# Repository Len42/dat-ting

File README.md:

# dat ting

_Multi-function Eurorack module inspired by [dis ting](https://www.expert-sleepers.co.uk/disting.html)_

**dat ting** is a digital multi-function 10 HP Eurorack module using a [Daisy Seed](https://electro-smith.com/products/daisy-seed). Part of my [homebrew Eurorack synthesizer](https://lenp.net/synth/).

[See here](https://lenp.net/synth/dat-ting/) for more info.

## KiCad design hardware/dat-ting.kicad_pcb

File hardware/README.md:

# dat ting

**dat ting** is a digital multi-function 10 HP Eurorack module using a [Daisy Seed](https://electro-smith.com/products/daisy-seed).

[See here](https://lenp.net/synth/dat-ting/hardware.html) for more info.

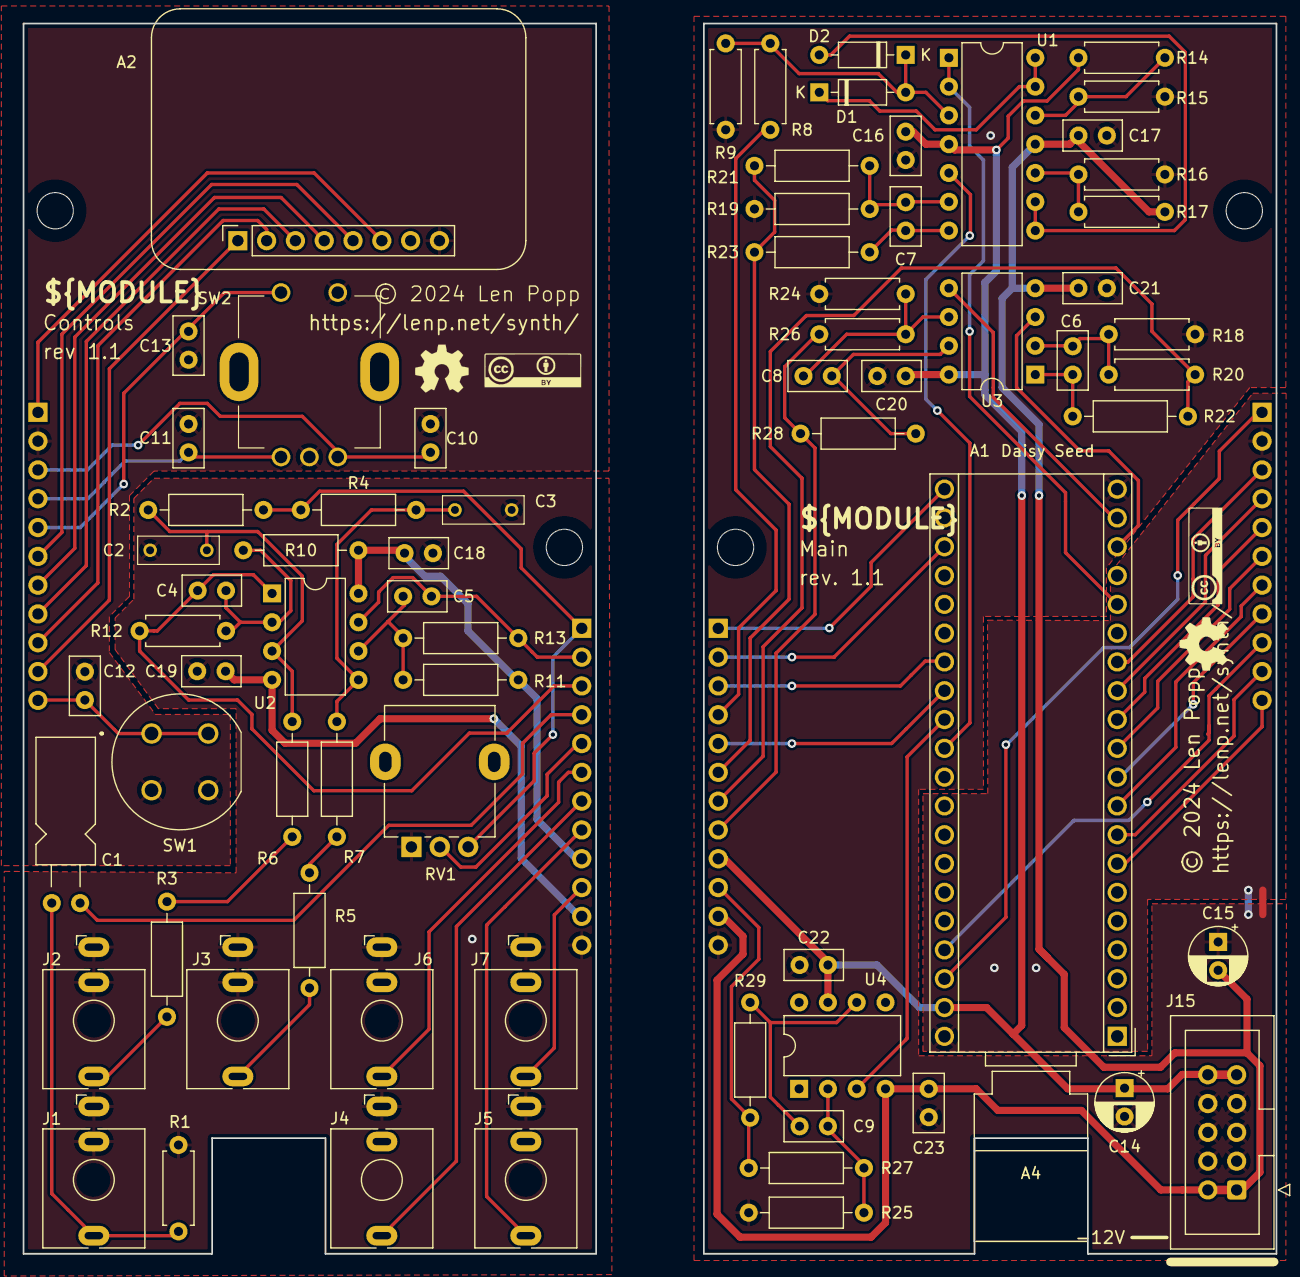
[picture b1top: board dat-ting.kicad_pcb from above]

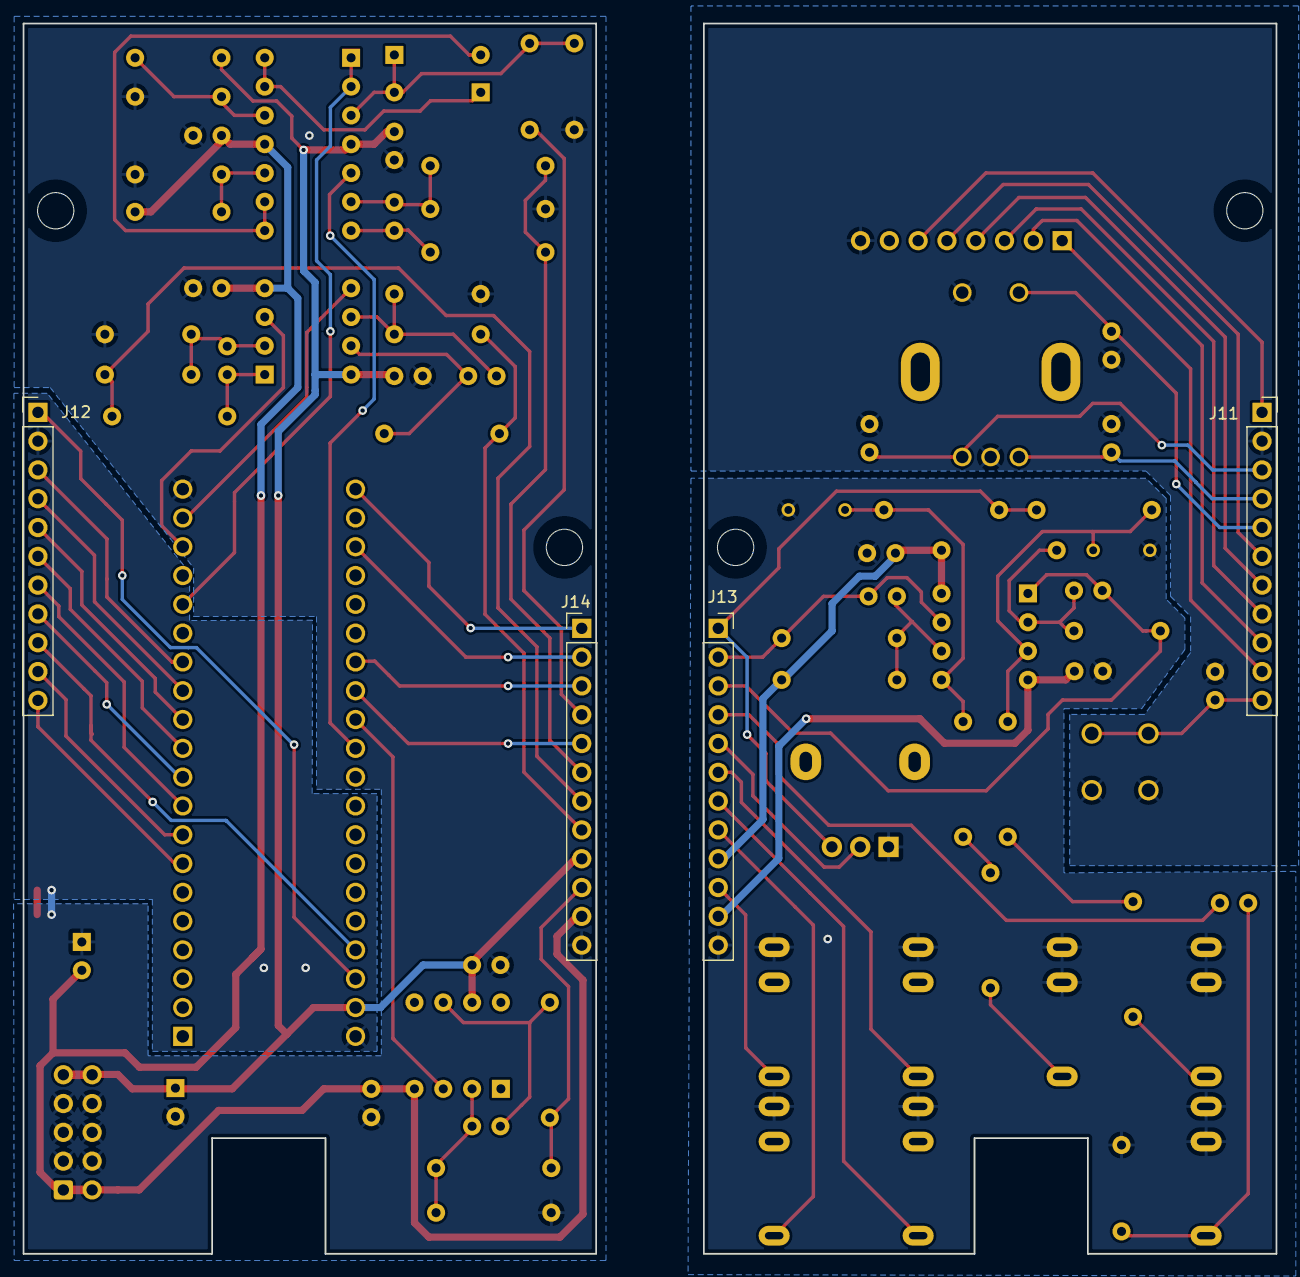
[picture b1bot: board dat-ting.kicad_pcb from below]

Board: 2 copper layers, 110.5 x 108.5 mm, 84 parts (4 on the bottom side), 49 nets.

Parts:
A1: Daisy_Seed; Module_Daisy_Seed
A2: OLED_SPI_128x32; OLED_SPI_128x32_0.91in_NoHoles
A4: Micro USB Adapter 90deg; USB-Micro-Adapter-90-Outline
C1: 4U7; C_Radial_L11.0mm_D5.0mm_P2.50mm_Horiz
C2, C3: 3N3; C_Rect_Kemet_L7.2mm_W2.5mm_P5mm
C4, C5: 5P6; C_Disc_D5.0mm_W2.5mm_P2.50mm
C6, C7, C8, C9: 47P; C_Disc_D5.0mm_W2.5mm_P2.50mm
C10, C11, C12, C13, C16, C17, C18, C19, C20, C21, C22, C23: 100N; C_Disc_D5.0mm_W2.5mm_P2.50mm
C14, C15: 10U; CP_Radial_D5.0mm_P2.50mm
D1, D2: 1N5711; D_DO-35_SOD27_P7.62mm_Horizontal
G1, G2: LOGO; Logo_CC_BY
G3, G4: LOGO; Logo_OSHW
H2, H4, H7, H9: MountingHole_M3; MountingHole_PCB_3.2mm_M3
J1, J2, J3, J4, J5, J6, J7: WQP-PJ398; Jack_3.5mm_QingPu_WQP-PJ398SM_Vertical
J11: Conn_Front_Left; PinSocket_1x11_P2.54mm_Vertical
J12: Conn_Back_Right; PinHeader_1x11_P2.54mm_Vertical
J13: Conn_Front_Right; PinSocket_1x12_P2.54mm_Vertical
J14: Conn_Back_Left; PinHeader_1x12_P2.54mm_Vertical
J15: Conn_Eurorack_10; IDC-Header-Eurorack-10-TH
R1: 1M; R_Axial_DIN0207_L6.3mm_D2.5mm_P7.62mm_Horizontal
R2, R4: 33K; R_Axial_DIN0207_L6.3mm_D2.5mm_P10.16mm_Horizontal
R3, R5, R6, R7: 120K; R_Axial_DIN0207_L6.3mm_D2.5mm_P10.16mm_Horizontal
R8, R20, R26: 100K; R_Axial_DIN0207_L6.3mm_D2.5mm_P7.62mm_Horizontal
R9: 33K; R_Axial_DIN0207_L6.3mm_D2.5mm_P7.62mm_Horizontal
R10, R11: 160K; R_Axial_DIN0207_L6.3mm_D2.5mm_P10.16mm_Horizontal
R12: 22K; R_Axial_DIN0207_L6.3mm_D2.5mm_P7.62mm_Horizontal
R13: 22K; R_Axial_DIN0207_L6.3mm_D2.5mm_P10.16mm_Horizontal
R14, R17: 130K; R_Axial_DIN0207_L6.3mm_D2.5mm_P7.62mm_Horizontal
R15, R16: 20K; R_Axial_DIN0207_L6.3mm_D2.5mm_P7.62mm_Horizontal
R18, R24: 36K; R_Axial_DIN0207_L6.3mm_D2.5mm_P7.62mm_Horizontal
R19, R25: 100K; R_Axial_DIN0207_L6.3mm_D2.5mm_P10.16mm_Horizontal
R21, R27: 200K; R_Axial_DIN0207_L6.3mm_D2.5mm_P10.16mm_Horizontal
R22, R23, R28, R29: 51R; R_Axial_DIN0207_L6.3mm_D2.5mm_P10.16mm_Horizontal
RV1: 100K; Potentiometer_Alpha_RD901F-40-00D_Single_Vertical
SW1: C&K_D6R; SW_Push_C&K_D6R
SW2: PEC11R; Encoder_Bourns_PEC11R_Switch
U1: TL074; DIP-14_W7.62mm
U2, U3: TL072; DIP-8_W7.62mm
U4: TL071; DIP-8_W7.62mm

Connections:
+3V3: A1.38 (3v3D), A2.6 (VIN), J11.1, J12.1
+3V3REF: A1.21 (3v3A), J13.1, J14.1, R2.1, R4.1, RV1.3
+12V: A1.39 (VIN), C14.1, C16.1, C18.1, C20.1, C22.1, J13.9, J14.9, J15.9 (+12V), J15.10, R10.2, R11.2, R14.1, U1.4 (V+), U2.8 (V+), U3.8 (V+), U4.7 (V+)
-12V: C15.2, C17.2, C19.2, C21.2, C23.2, J13.11, J14.11, J15.1 (-12V), J15.2, R17.1, U1.11 (V-), U2.4 (V-), U3.4 (V-), U4.4 (V-)
/+CLAMP: D1.1 (K), U1.13 (-), U1.14
/-CLAMP: D2.2 (A), U1.8, U1.9 (-)
ENC-A: A1.13 (D12), C11.1, J11.4, J12.4, SW2.A
ENC-B: A1.14 (D13), C10.1, J11.3, J12.3, SW2.B
ENC-SW: A1.12 (D11), C13.1, J11.5, J12.5, SW2.S1
GND: A1.20 (AGND), A1.40 (GND), A2.8 (GND), C2.2, C3.2, C10.2, C11.2, C12.2, C13.2, C14.2, C15.1, C16.2, C17.1, C18.2, C19.1, C20.2, C21.1, C22.2, C23.1, J1.S, J1.TN, J2.S, J2.TN, J3.S, J3.TN, J4.S, J5.S, J6.S, J7.S, J11.2, J12.2, J13.12, J14.12, J15.3 (GND), J15.4, J15.5 (GND), J15.6, J15.7 (GND), J15.8, R1.2, R9.2, R15.2, R16.2, R18.2, R19.2, R24.2, R25.2, RV1.1, SW1.3, SW1.4, SW2.C, SW2.S2
IN-AUDIO: C1.1, J13.4, J14.4, R8.1
unnamed: C1.2, J1.T, R1.1
unnamed: C6.2, R22.1, U3.1
unnamed: C7.2, R23.1, U1.7
unnamed: C8.2, R28.1, U3.7
unnamed: C9.2, R29.1, U4.6
unnamed: D1.2 (A), D2.1 (K), R8.2, R9.1, U1.3 (+)
unnamed: J2.T, R3.1
unnamed: J3.T, R5.1
unnamed: R3.2, R6.1
unnamed: R5.2, R7.1
unnamed: C7.1, R19.1, R21.1, U1.6 (-)
unnamed: R16.1, R17.2, U1.10 (+)
unnamed: R14.2, R15.1, U1.12 (+)
unnamed: C2.1, R2.2, R6.2, U2.3 (+)
unnamed: C4.1, R10.1, R12.1, U2.2 (-)
unnamed: C3.1, R4.2, R7.2, U2.5 (+)
unnamed: C5.1, R11.1, R13.1, U2.6 (-)
unnamed: C6.1, R18.1, R20.1, U3.2 (-)
unnamed: C8.1, R24.1, R26.1, U3.6 (-)
unnamed: C9.1, R25.1, R27.1, U4.2 (-)
OLED-CD: A1.10 (SPI1_MISO), A2.3 (DC), J11.8, J12.8
OLED-CS: A1.8 (SPI1_NSS), A2.1 (CS), J11.10, J12.10
OLED-DATA: A1.11 (SPI1_MOSI), A2.5 (SDA), J11.6, J12.6
OLED-RST: A1.37 (D30), A2.2 (RESET), J11.9, J12.9
OLED-SCK: A1.9 (SPI1_SCK), A2.4 (SCL), J11.7, J12.7
OUT-AUDIO-L: J4.T, J13.7, J14.7, R20.2, R22.2
OUT-AUDIO-R: J5.T, J13.8, J14.8, R26.2, R28.2
OUT-CV-1: J6.T, J13.6, J14.6, R21.2, R23.2
OUT-CV-2: J7.T, J13.10, J14.10, R27.2, R29.2
SEED-IN-AUDIO: A1.16 (AUDIO_IN_L), U1.1, U1.2 (-)
SEED-IN-CV-1: A1.27 (A5), C4.2, J13.3, J14.3, R12.2, U2.1
SEED-IN-CV-2: A1.23 (A1), C5.2, J13.2, J14.2, R13.2, U2.7
SEED-IN-CV-POT: A1.28 (A6), J13.5, J14.5, RV1.2
SEED-IN-SW: A1.7 (D6), C12.1, J11.11, J12.11, SW1.1, SW1.2
SEED-OUT-AUDIO-L: A1.18 (AUDIO_OUT_L), U3.3 (+)
SEED-OUT-AUDIO-R: A1.19 (AUDIO_OUT_R), U3.5 (+)
SEED-OUT-CV-1: A1.30 (DAC1_OUT1), U1.5 (+)
SEED-OUT-CV-2: A1.29 (DAC1_OUT2), U4.3 (+)

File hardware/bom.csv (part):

"Reference","Qty","Value","Value2","Note","Description","Datasheet","Manufacturer","ManufacturerPartNum","Distributor","DistributorPartNum","DistributorPartLink","Distributor2","DistributorPartNum2","DistributorPartLink2","Distributor3","DistributorPartNum3","DistributorPartLink3"
"A1","1","Daisy_Seed","","","Electrosmith Daisy Seed DSP Microcontroller Module ARM Cortex-M7","https://daisy.nyc3.cdn.digitaloceanspaces.com/products/seed/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","Electrosmith","","Electrosmith","","https://electro-smith.com/products/daisy-seed","Thonk","PCB_Daisy_Seed","https://www.thonk.co.uk/shop/electrosmith-daisy-seed/","","",""
"A2","1","OLED_SPI_128x32","","","OLED display module 128x32 pixels SPI with header","https://learn.adafruit.com/monochrome-oled-breakouts","Adafruit","661","Adafruit","661","https://www.adafruit.com/product/661","","","","","",""
"A3","1","Cable_Eurorack_10","","Length as required","Eurorack 16-10 pin power cable","","","","Thonk","","https://www.thonk.co.uk/shop/eurorack-power-cables/","SynthCube","","https://synthcube.com/cart/eurorack-ribbon-power-cables","Modular Addict","","https://modularaddict.com/parts/eurorack-power-cables-1"
"A4","1","Micro USB Adapter 90deg","","","Micro USB adapter/cable, 90 deg.","","StarTech","","Amazon","","https://www.amazon.ca/dp/B00EANUQ5M","","","","","",""
"C1","1","4U7","","","Capacitor - Non-polarized Electrolytic","https://www.mouser.ca/datasheet/2/315/ABA0000C1053-947510.pdf","Panasonic","ECE-A1HN4R7U","Mouser","667-ECE-A1HN4R7U","https://www.mouser.ca/ProductDetail/667-ECE-A1HN4R7U","","","","","",""
"C2 C3","2","3N3","","","Capacitor - Film","https://www.mouser.ca/datasheet/2/447/KEM_F3101_R82-3316969.pdf","KEMET","R82EC1330AA50K","Mouser","80-R82EC1330AA50K","https://www.mouser.ca/ProductDetail/KEMET/R82EC1330AA50K?qs=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","","","","","",""
"C4 C5","2","5P6","C0G/NP0","","Capacitor - Ceramic","https://www.mouser.ca/datasheet/2/212/KEM_C1049_GOLDMAX_C0G-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","KEMET","C315C569D1G5TA","Mouser","80-C315C569D1G","https://www.mouser.ca/ProductDetail/?qs=qe%2F8UmbcoTBh6wC284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","","","","","",""
"C6 C7 C8 C9","4","47P","C0G/NP0","","Capacitor - Ceramic","https://www.vishay.com/docs/45171/kseries.pdf","Vishay","K470K15C0GH53L2","Mouser","594-K470K15C0GH53L2","https://www.mouser.ca/ProductDetail/Vishay-BC-Components/K47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","","","","","",""
"C10 C11 C12 C13 C16 C17 C18 C19 C20 C21 C22 C23","12","100N","","IC decoupling","-- mixed values --","https://product.tdk.com/system/files/dam/doc/product/capacit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","TDK","FG18X7R1H104KNT06","Mouser","810-FG18X7R1H104KNT6","https://www.mouser.ca/ProductDetail/810-FG18X7R1H104KNT6","","","","","",""
"C14 C15","2","10U","35 VDC","12 V decoupling","Capacitor - Electrolytic - 12 V decoupling","https://www.mouser.ca/datasheet/2/315/ABA0000C1059-947582.pdf","Panasonic","ECE-A1VKS100I","Mouser","667-ECE-A1VKS100I","https://www.mouser.ca/ProductDetail/667-ECE-A1VKS100I","Thonk","Group_Eurorack_DIY_Essential","https://www.thonk.co.uk/shop/eurorack-diy-essentials/","","",""
"D1 D2","2","1N5711","","","Schottky signal diode","https://www.mouser.ca/datasheet/2/389/cd00000759-1795802.pdf","STMicroelectronics","1N5711","Mouser","511-1N5711","https://www.mouser.ca/ProductDetail/STMicroelectronics/1N571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","","","","","",""
"H1 H5 H6 H10","4","HW_Screw_M3x0.50x6","","","Machine screw, M3x0.50x6","~","","","","","","","","","","",""
"H3 H8","2","HW_Standoff_F-F_11mm_M3x0.50","","","Standoff, 11mm, female-female, M3x0.50","https://www.thonk.co.uk/wp-content/uploads/2018/05/standoff-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","Ettinger","05.03.111","Thonk","Mech_11mm_Standoff_(x10)","https://www.thonk.co.uk/shop/standoffs/","Mouser","710-970110321","https://www.mouser.ca/ProductDetail/Wurth-Elektronik/9701103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","Mouser","144-MTS-11","https://www.mouser.ca/ProductDetail/144-MTS-11"
"J1 J2 J3 J4 J5 J6 J7","7","WQP-PJ398","","","Audio Jack, 2 Poles (Mono / TS), Switched T Pole (Normalling), QingPu / Thonkiconn","http://www.qingpu-electronics.com/en/products/WQP-PJ398SM-362.html","QingPu / Thonk","PJ398SM / WQP518MA","Thonk","PJ398SM","https://www.thonk.co.uk/shop/thonkiconn/","SynthCube","WQP518MA","https://synthcube.com/cart/3-5mm-euro-jacks","Adafruit","4031","https://www.adafruit.com/product/4031"
"J8 J9","2","Conn_01x20","","","Pin socket connector, single row, 01x08","https://cdn-shop.adafruit.com/datasheets/00548.pdf","","","Adafruit","598","https://www.adafruit.com/product/598","Mouser","710-61303211821","https://www.mouser.ca/ProductDetail/Wurth-Elektronik/6130321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","","",""
"J10","1","Conn_01x08","","OLED module needs a header connector with 8mm pins","","https://www.amphenol-icc.com/media/wysiwyg/files/documentati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","Amphenol FCI","10129378-936003BLF","Mouser","649-1012937893603BLF","https://www.mouser.ca/ProductDetail/Amphenol-FCI/10129378-93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","","","","","",""
"J11","1","Conn_Front_Left","","","Generic connector, single row, 01x11, script generated (kicad-library-utils/schlib/autogen/connector/)","https://cdn-shop.adafruit.com/datasheets/00548.pdf","","","Adafruit","598","https://www.adafruit.com/product/598","Mouser","710-61303211821","https://www.mouser.ca/ProductDetail/Wurth-Elektronik/6130321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","","",""
"J12","1","Conn_Back_Right","","","Generic connector, single row, 01x11, script generated (kicad-library-utils/schlib/autogen/connector/)","https://www.amphenol-icc.com/media/wysiwyg/files/documentati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","","","Adafruit","392","https://www.adafruit.com/product/392","Mouser","649-1012937893601BLF","https://www.mouser.ca/ProductDetail/649-1012937893601BLF","","",""
"J13","1","Conn_Front_Right","","","Generic connector, single row, 01x12, script generated (kicad-library-utils/schlib/autogen/connector/)","https://cdn-shop.adafruit.com/datasheets/00548.pdf","","","Adafruit","598","https://www.adafruit.com/product/598","Mouser","710-61303211821","https://www.mouser.ca/ProductDetail/Wurth-Elektronik/6130321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","","",""
"J14","1","Conn_Back_Left","","","Generic connector, single row, 01x12, script generated (kicad-library-utils/schlib/autogen/connector/)","https://www.amphenol-icc.com/media/wysiwyg/files/documentati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","","","Adafruit","392","https://www.adafruit.com/product/392","Mouser","649-1012937893601BLF","https://www.mouser.ca/ProductDetail/649-1012937893601BLF","","",""
"J15","1","Conn_Eurorack_10","","","Eurorack 10-pin board power connector","https://www.mouser.ca/datasheet/2/445/61201021621-1717731.pdf","Wurth Elektronik","61201021621","Mouser","710-61201021621","https://www.mouser.ca/ProductDetail/Wurth-Elektronik/6120102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","Thonk","","https://www.thonk.co.uk/shop/eurorack-diy-essentials/","","",""
"R1","1","1M","1%, 1/6 W","","Resistor","https://www.mouser.ca/datasheet/2/447/YAGEO_MFR_datasheet_20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","YAGEO","MFR-12FTF52-1M","Mouser","603-MFR-12FTF52-1M","https://www.mouser.ca/ProductDetail/YAGEO/MFR-12FTF52-1M?qs=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","","","","","",""
"R2 R4","2","33K","0.1%, 0.1W","","Resistor","https://www.mouser.ca/datasheet/2/447/Yageo_LR_MFP_1-1947926.pdf","YAGEO","MFP-25BRD52-33K","Mouser","603-MFP-25BRD52-33K","https://www.mouser.ca/ProductDetail/YAGEO/MFP-25BRD52-33K?qs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","","","","","",""
"R3 R5 R6 R7","4","120K","0.1%, 0.1W","Use 1 x 240K (0.1%) in place of 2 x 120K if available","Resistor","https://www.vishay.com/docs/31027/cmfmil.pdf","Vishay","RN55E1203BRE6","Mouser","71-RN55E1203BTR","https://www.mouser.ca/ProductDetail/Vishay-Dale/RN55E1203BRE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","","","","","",""
"R8 R20 R26","3","100K","1%, 1/6 W","","Resistor","https://www.mouser.ca/datasheet/2/447/YAGEO_MFR_datasheet_20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","YAGEO","MFR-12FRF52-100K","Mouser","603-MFR-12FRF52100K","https://www.mouser.ca/ProductDetail/YAGEO/MFR-12FRF52-100K?q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","","","","","",""
"R9","1","33K","1%, 1/6 W","","Resistor","https://www.mouser.ca/datasheet/2/447/YAGEO_MFR_datasheet_20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","YAGEO","MFR-12FTF52-33K","Mouser","603-MFR-12FTF52-33K","https://www.mouser.ca/ProductDetail/YAGEO/MFR-12FTF52-33K?qs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","","","","","",""
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
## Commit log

2024-11-07 Cleaned-up copy of the current dev repo
2024-11-07 Words.
2024-11-08 firmware: remove unused fields in ProcessArgs
2024-11-09 hardware: add schematic.pdf, update PCB photos
2024-11-10 firmware: update LICENSE, add a comment
2024-11-11 firmware: DataTable, LookupTable comments & cleanup & iterators
2024-11-15 firmware: doc comments, cleanup
2024-11-16 firmware: LICENSE correction
2024-11-18 firmware: Fix a UI bug
2024-11-18 firmware: Delay - LFO modulation
2024-11-19 firmware: Variable-shape VCO: pitch modulation from CV2
2024-11-19 README.md - fix the module name
2024-12-05 firmware: Misc changes: - Rename some functions for consistency - Fix a gate-off bug - add midValue() function
2025-01-01 Firmware is now built with gcc 14.2
2025-04-29 firmware: Use "deducing this" instead of CRTP for compile-time polymorphism. Because I like it better.

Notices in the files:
hardware/dat-ting.kicad_pcb:
Copyright © 2024 Len Popp CC BY
